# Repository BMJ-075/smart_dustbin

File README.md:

# smart_dustbin
smart dustbin is self operating and compressing dustbin in which we used IR sensor and a mechanical compressor to automatically open the hatch and compress the garbage if dustbin is full.

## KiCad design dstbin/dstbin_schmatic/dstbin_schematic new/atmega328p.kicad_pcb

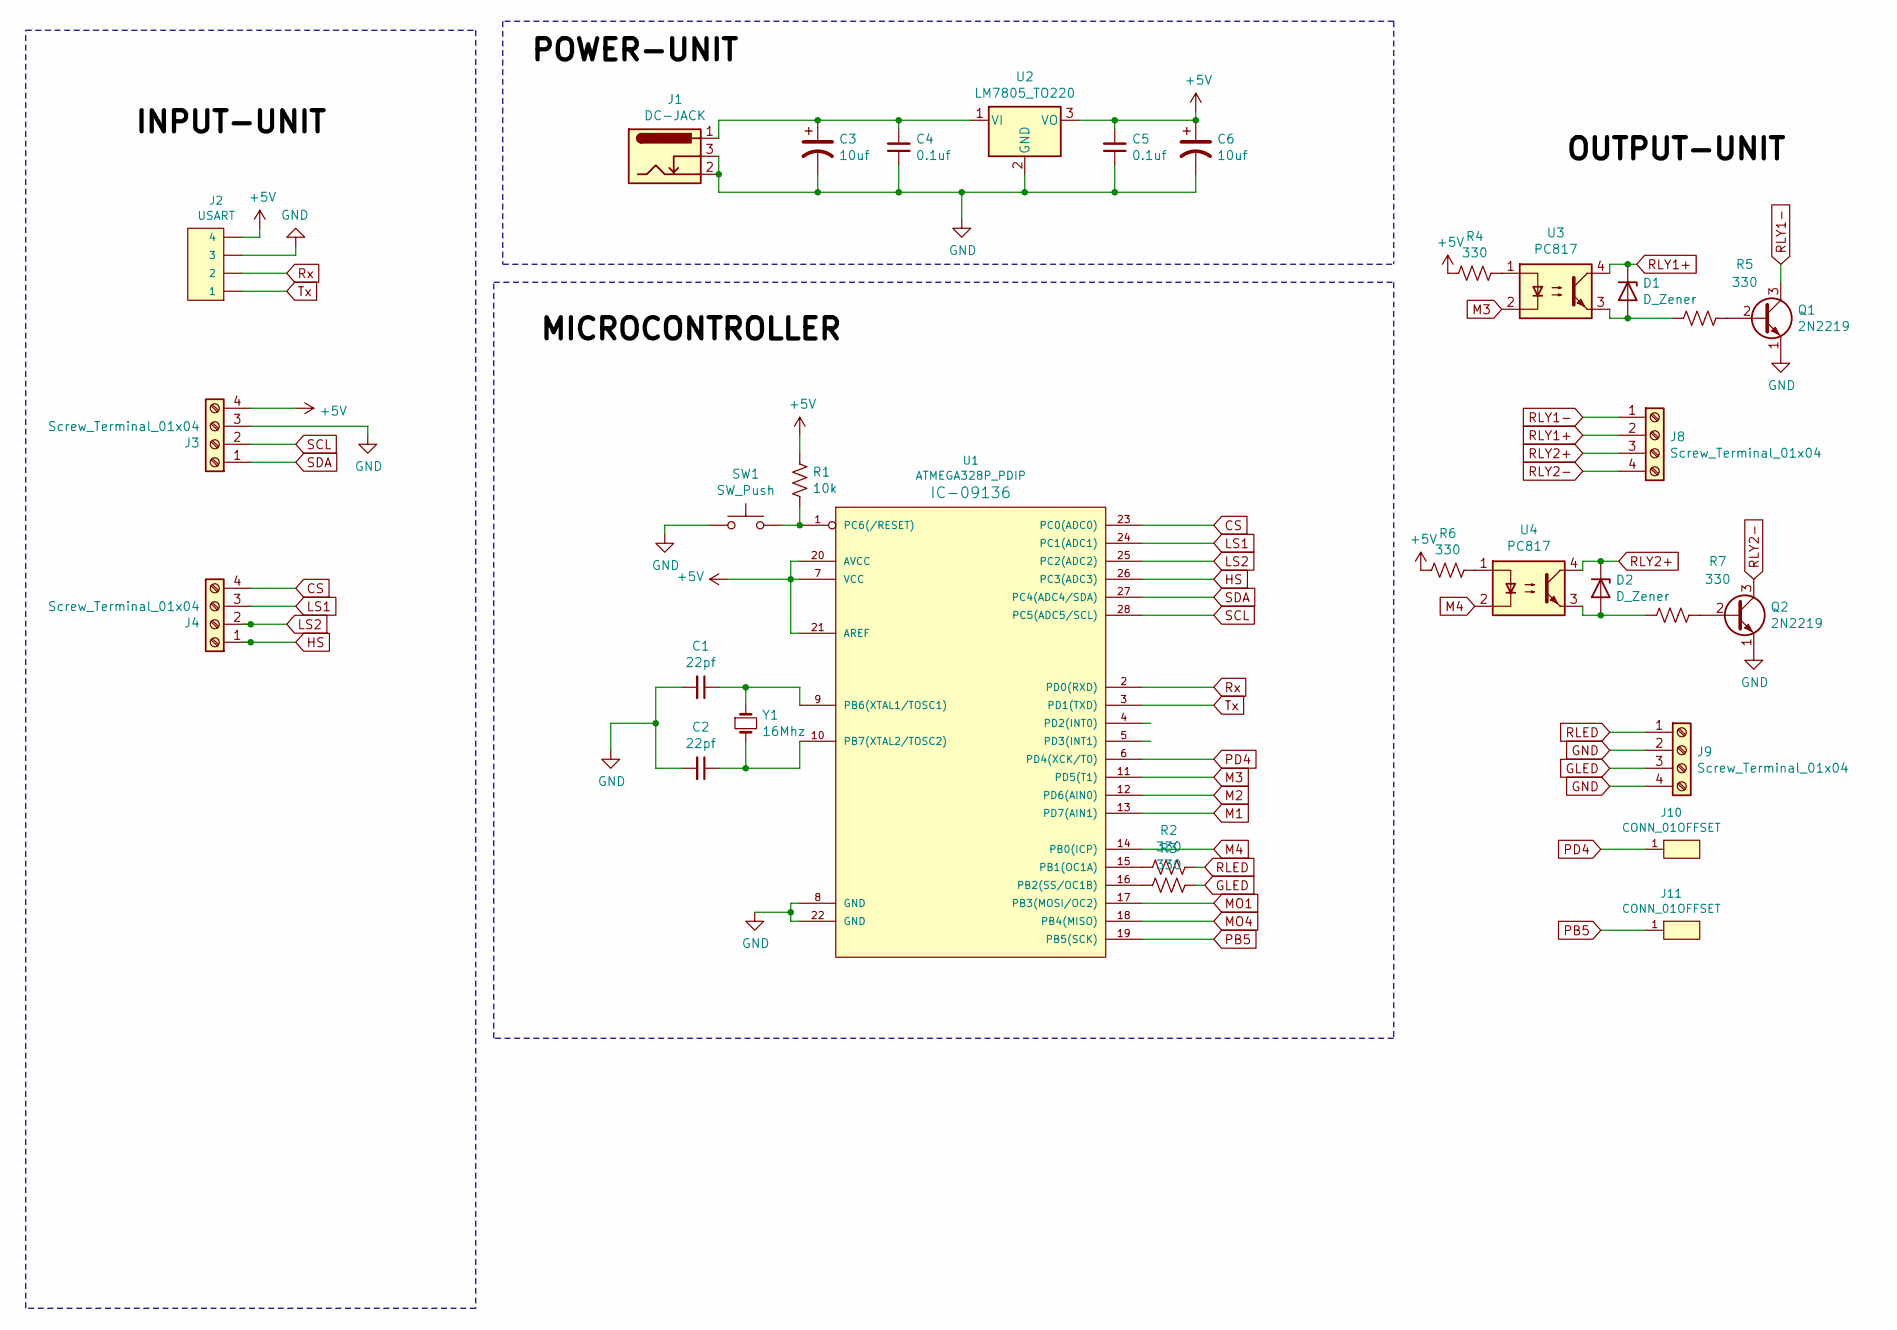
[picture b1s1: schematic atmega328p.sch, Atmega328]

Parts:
C1, C2: 22pf; C_Disc_D4.7mm_W2.5mm_P5.00mm
C3, C6: 10uf; CP_Radial_D5.0mm_P2.50mm
C4, C5: 0.1uf; C_Disc_D4.7mm_W2.5mm_P5.00mm
D1, D2: D_Zener; D_5W_P12.70mm_Horizontal
J1: DC-JACK; BarrelJack_Wuerth_6941xx301002
J2: USART; PinSocket_1x04_P2.54mm_Vertical
J3, J4, J8, J9: Screw_Terminal_01x04; TerminalBlock_Phoenix_MKDS-1,5-4-5.08_1x04_P5.08mm_Horizont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
J10, J11: CONN_01OFFSET; PinSocket_1x01_P2.54mm_Vertical
Q1, Q2: 2N2219; TO-39-3
R1: 10k; R_Axial_DIN0411_L9.9mm_D3.6mm_P15.24mm_Horizontal
R2, R3, R4, R5, R6, R7: 330; R_Axial_DIN0411_L9.9mm_D3.6mm_P15.24mm_Horizontal
SW1: SW_Push; SW_PUSH_6mm_H7.3mm
U1: ATMEGA328P_PDIP; DIP-28_W7.62mm_LongPads
U2: LM7805_TO220; TO-220-3_Vertical
U3, U4: PC817; DIP-4_W7.62mm
Y1: 16Mhz; Crystal_HC52-U_Vertical

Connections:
+5V: C5.2, C6.1, J2.4, J3.4, R1.1, R4.2, R6.2, U1.7 (VCC), U1.20 (AVCC), U1.21 (AREF), U2.3 (VO)
CS: J4.4, U1.23 (PC0(ADC0))
GLED: J9.3, R3.1
GND: C1.2, C2.2, C3.2, C4.1, C5.1, C6.2, J1.2, J1.3, J2.3, J3.3, J9.2, J9.4, Q1.1 (E), Q2.1 (E), SW1.1, U1.8 (GND), U1.22 (GND), U2.2 (GND)
HS: J4.1, U1.26 (PC3(ADC3))
LS1: J4.3, U1.24 (PC1(ADC1))
LS2: J4.2, U1.25 (PC2(ADC2))
M1: U1.13 (PD7(AIN1))
M2: U1.12 (PD6(AIN0))
M3: U1.11 (PD5(T1)), U3.2
M4: U1.14 (PB0(ICP)), U4.2
MO1: U1.17 (PB3(MOSI/OC2))
MO4: U1.18 (PB4(MISO))
unnamed: C1.1, U1.9 (PB6(XTAL1/TOSC1)), Y1.1
unnamed: C2.1, U1.10 (PB7(XTAL2/TOSC2)), Y1.2
unnamed: C3.1, C4.2, J1.1, U2.1 (VI)
unnamed: D1.2 (A), R5.2, U3.3
unnamed: D2.2 (A), R7.2, U4.3
unnamed: Q1.2 (B), R5.1
unnamed: Q2.2 (B), R7.1
unnamed: R1.2, SW1.2, U1.1 (PC6(/RESET))
unnamed: R2.2, U1.15 (PB1(OC1A))
unnamed: R3.2, U1.16 (PB2(SS/OC1B))
unnamed: R4.1, U3.1
unnamed: R6.1, U4.1
PB5: J11.1, U1.19 (PB5(SCK))
PD4: J10.1, U1.6 (PD4(XCK/T0))
RLED: J9.1, R2.1
RLY1+: D1.1 (K), J8.2, U3.4
RLY1-: J8.1, Q1.3 (C)
RLY2+: D2.1 (K), J8.3, U4.4
RLY2-: J8.4, Q2.3 (C)
Rx: J2.2, U1.2 (PD0(RXD))
SCL: J3.2, U1.28 (PC5(ADC5/SCL))
SDA: J3.1, U1.27 (PC4(ADC4/SDA))
Tx: J2.1, U1.3 (PD1(TXD))

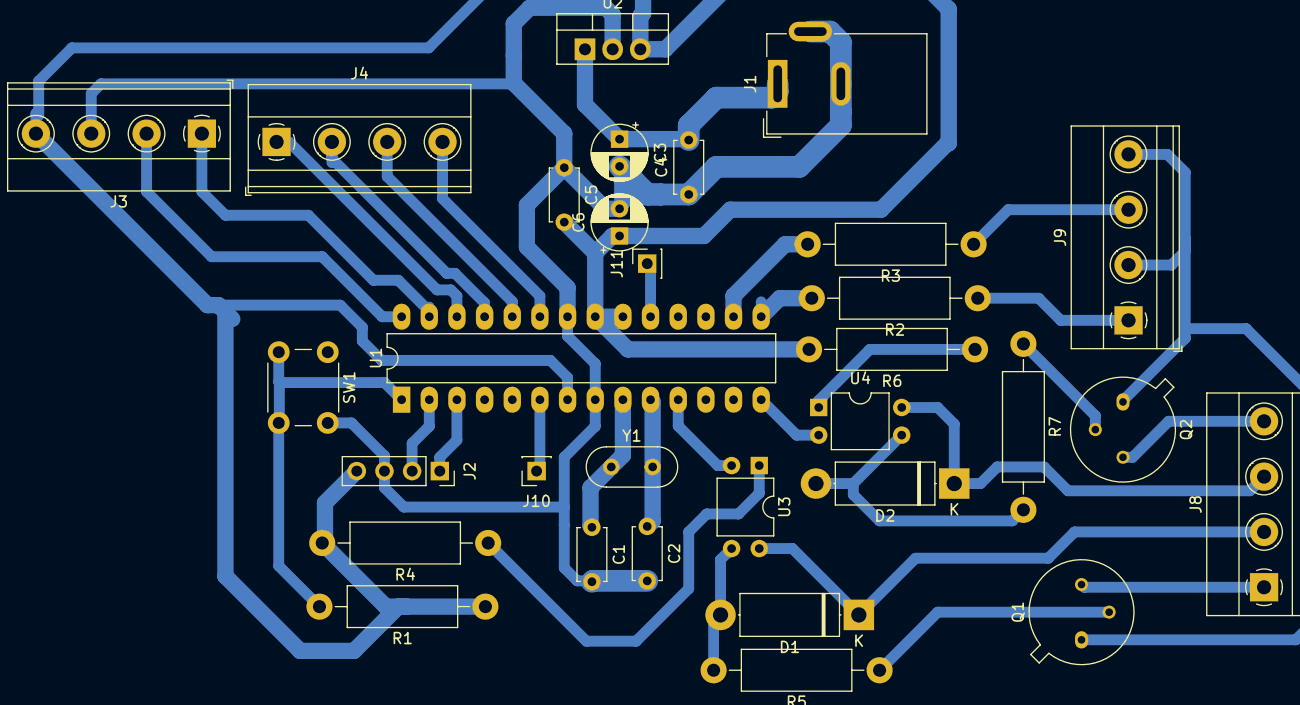
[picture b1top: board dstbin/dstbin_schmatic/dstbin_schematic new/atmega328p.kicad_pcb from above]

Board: 2 copper layers, 31 parts (0 on the bottom side), 32 nets.

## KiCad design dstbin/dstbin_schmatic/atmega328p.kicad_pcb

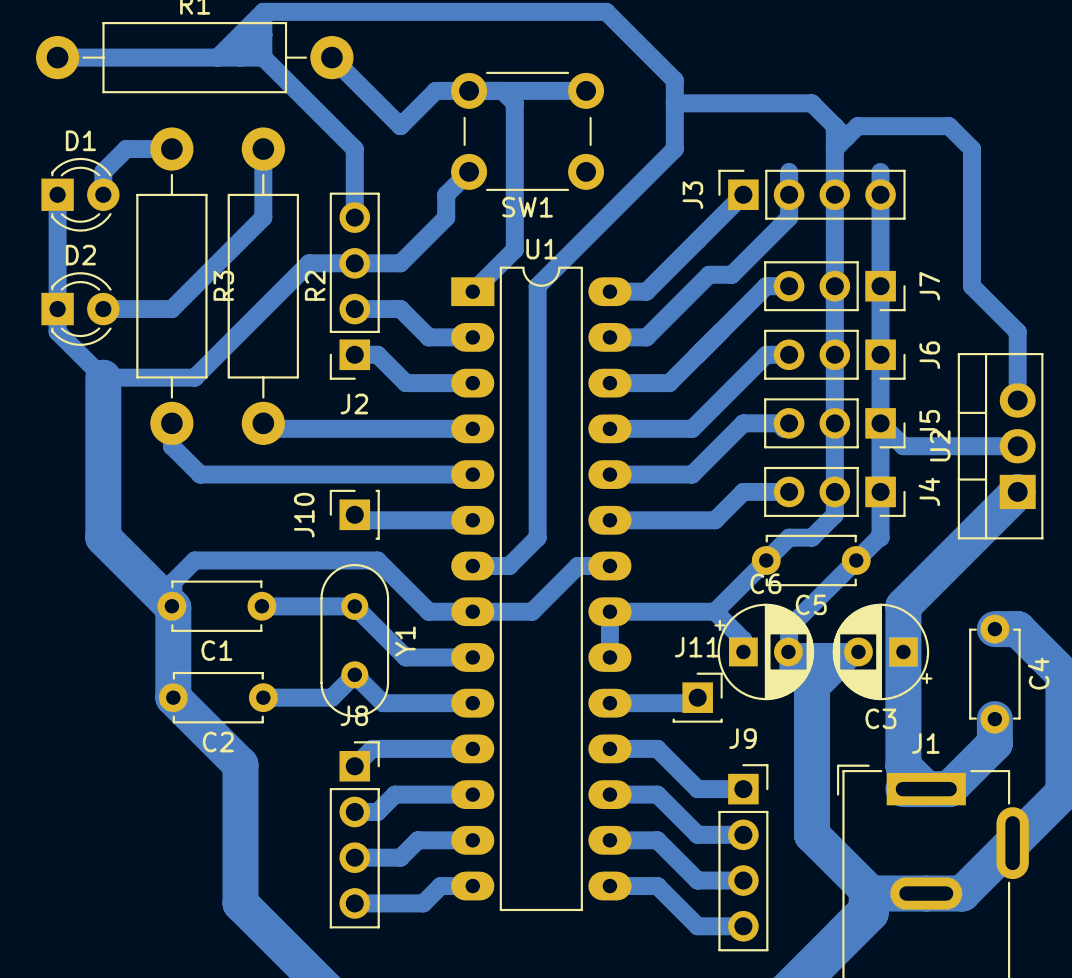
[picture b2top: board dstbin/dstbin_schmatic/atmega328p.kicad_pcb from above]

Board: 2 copper layers, 26 parts (0 on the bottom side), 28 nets.

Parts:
C1, C2: 22pf; C_Disc_D4.7mm_W2.5mm_P5.00mm
C3, C6: 10uf; CP_Radial_D5.0mm_P2.50mm
C4, C5: 0.1uf; C_Disc_D4.7mm_W2.5mm_P5.00mm
D1, D2: LED; LED_D3.0mm
J1: DC-JACK; BarrelJack_Wuerth_6941xx301002
J2: USART; PinSocket_1x04_P2.54mm_Vertical
J3: I2C; PinSocket_1x04_P2.54mm_Vertical
J4: CURRENT SENSOR; PinSocket_1x03_P2.54mm_Vertical
J5, J6: IR SENSOR; PinSocket_1x03_P2.54mm_Vertical
J7: HALLEFFECT; PinSocket_1x03_P2.54mm_Vertical
J8, J9: CONN_04LOCK; PinSocket_1x04_P2.54mm_Vertical
J10, J11: CONN_01OFFSET; PinSocket_1x01_P2.54mm_Vertical
R1: 10k; R_Axial_DIN0411_L9.9mm_D3.6mm_P15.24mm_Horizontal
R2, R3: 330; R_Axial_DIN0411_L9.9mm_D3.6mm_P15.24mm_Horizontal
SW1: SW_Push; SW_PUSH_6mm_H7.3mm
U1: ATMEGA328P_PDIP; DIP-28_W7.62mm_LongPads
U2: LM7805_TO220; TO-220-3_Vertical
Y1: 16Mhz; Crystal_HC52-U_Vertical

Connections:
+5V: C5.2, C6.1, J2.4, J3.3, J4.2, J5.2, J6.2, J7.2, R1.1, U1.7, U1.20, U1.21, U2.3
CS: J4.3, U1.23
GLED: D1.2, R3.1
GND: C1.2, C2.2, C3.2, C4.1, C5.1, C6.2, D1.1, D2.1, J1.2, J1.3, J2.3, J3.4, J4.1, J5.1, J6.1, J7.1, SW1.1, U1.8, U1.22, U2.2
HS: J7.3, U1.26
LS1: J5.3, U1.24
LS2: J6.3, U1.25
M1: J8.3, U1.13
M2: J8.2, U1.12
M3: J8.1, U1.11
M4: J8.4, U1.14
MO1: J9.2, U1.17
MO2: J9.3, U1.16
MO3: J9.4, U1.15
MO4: J9.1, U1.18
unnamed: C1.1, U1.9, Y1.1
unnamed: C2.1, U1.10, Y1.2
unnamed: C3.1, C4.2, J1.1, U2.1
unnamed: R1.2, SW1.2, U1.1
unnamed: R2.2, U1.4
unnamed: R3.2, U1.5
PB5: J11.1, U1.19
PD4: J10.1, U1.6
RLED: D2.2, R2.1
Rx: J2.2, U1.2
SCL: J3.1, U1.28
SDA: J3.2, U1.27
Tx: J2.1, U1.3
